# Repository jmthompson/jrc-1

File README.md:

JRC-1
=====

The JRC-1 (Josh's Retro Computer 1) the first in my new series of homebrew
retro computers. It is the first in the JRC series and is the successor to
COLE-1 and COLE-2.

The primary goal for this project is to scale back some of the lofty goals set
for its predecessor, and instead provide some limited expansion capabilities
so that features can be added iteratively down the road.

More information is available on the JRC-1 section of my blog at
https://www.area73.us/jrc-1.

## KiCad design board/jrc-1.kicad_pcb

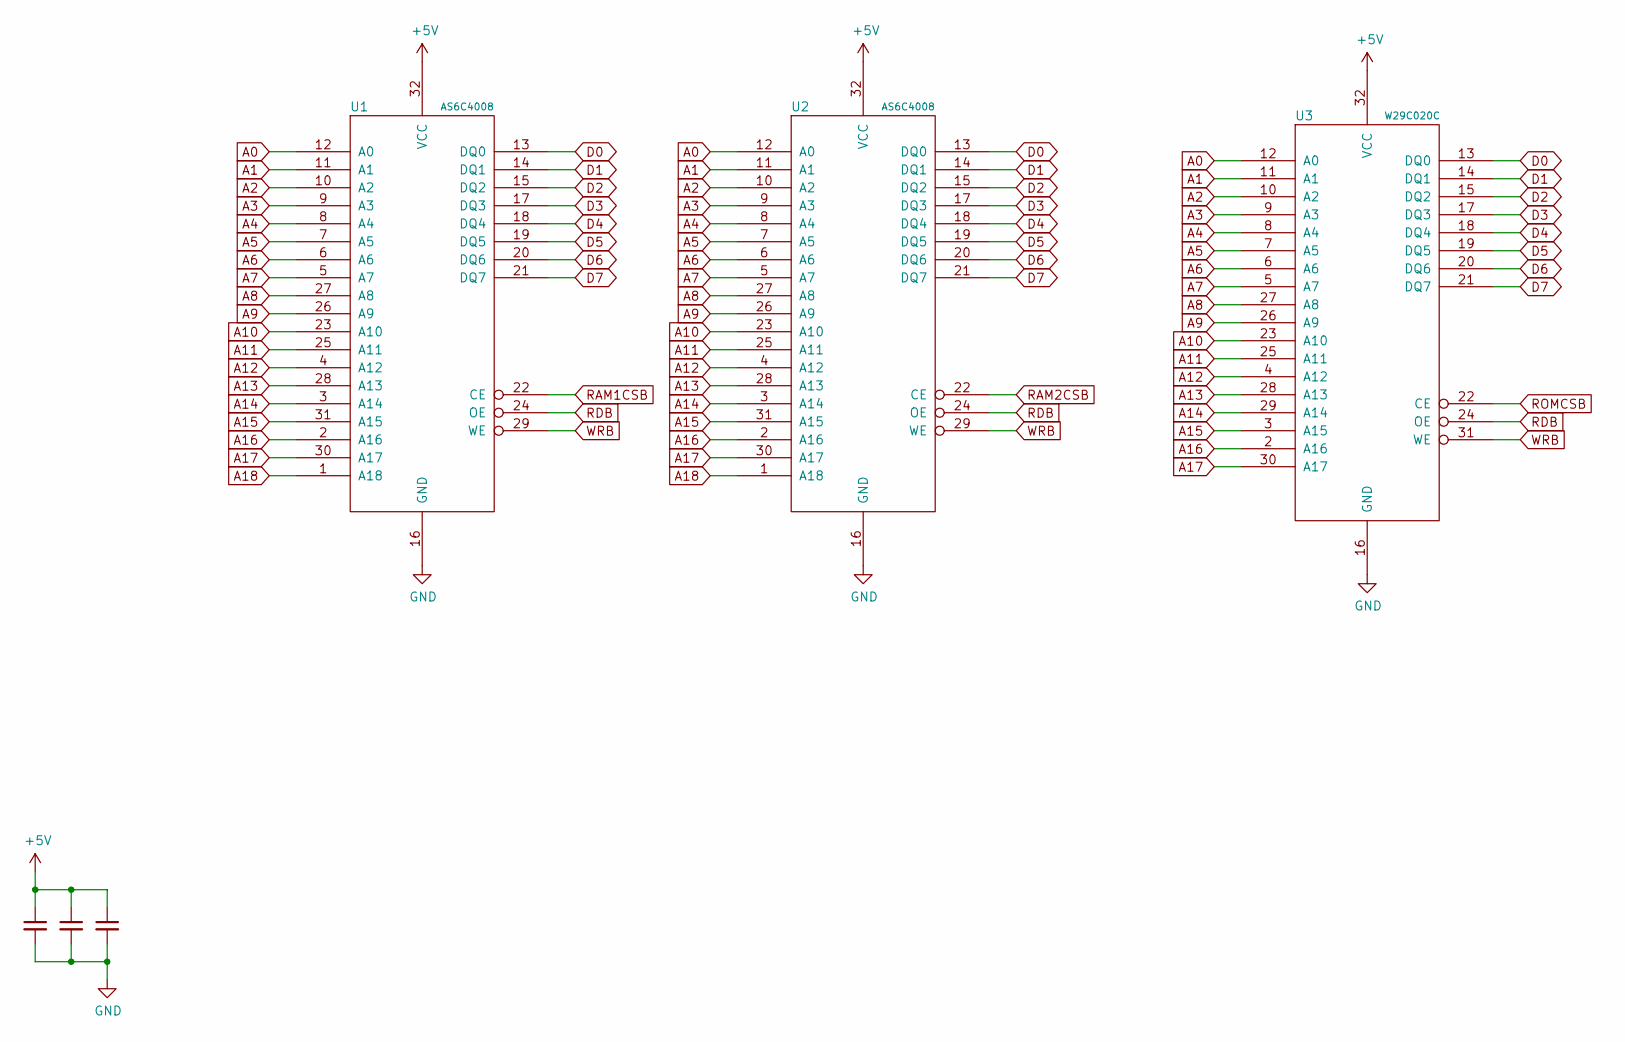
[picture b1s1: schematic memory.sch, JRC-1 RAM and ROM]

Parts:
C1, C2, C3: 0.1u; C_Rect_L4.6mm_W2.0mm_P2.50mm_MKS02_FKP02
U1, U2: AS6C4008; DIP-32_W15.24mm_Socket
U3: W29C020C; DIP_Socket-32_W11.9_W12.7_W15.24_W17.78_W18.5_3M_232-1285-0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

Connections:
+5V: C1.1, C2.1, C3.1, U1.32 (VCC), U2.32 (VCC), U3.32 (VCC); also elsewhere on the board
A0: U1.12 (A0), U2.12 (A0), U3.12 (A0); also elsewhere on the board
A1: U1.11 (A1), U2.11 (A1), U3.11 (A1); also elsewhere on the board
A2: U1.10 (A2), U2.10 (A2), U3.10 (A2); also elsewhere on the board
A3: U1.9 (A3), U2.9 (A3), U3.9 (A3); also elsewhere on the board
A4: U1.8 (A4), U2.8 (A4), U3.8 (A4); also elsewhere on the board
A5: U1.7 (A5), U2.7 (A5), U3.7 (A5); also elsewhere on the board
A6: U1.6 (A6), U2.6 (A6), U3.6 (A6); also elsewhere on the board
A7: U1.5 (A7), U2.5 (A7), U3.5 (A7); also elsewhere on the board
A8: U1.27 (A8), U2.27 (A8), U3.27 (A8); also elsewhere on the board
A9: U1.26 (A9), U2.26 (A9), U3.26 (A9); also elsewhere on the board
A10: U1.23 (A10), U2.23 (A10), U3.23 (A10); also elsewhere on the board
A11: U1.25 (A11), U2.25 (A11), U3.25 (A11); also elsewhere on the board
A12: U1.4 (A12), U2.4 (A12), U3.4 (A12); also elsewhere on the board
A13: U1.28 (A13), U2.28 (A13), U3.28 (A13); also elsewhere on the board
A14: U1.3 (A14), U2.3 (A14), U3.29 (A14); also elsewhere on the board
A15: U1.31 (A15), U2.31 (A15), U3.3 (A15); also elsewhere on the board
A16: U1.2 (A16), U2.2 (A16), U3.2 (A16); also elsewhere on the board
A17: U1.30 (A17), U2.30 (A17), U3.30 (A17); also elsewhere on the board
A18: U1.1 (A18), U2.1 (A18); also elsewhere on the board
D0: U1.13 (DQ0), U2.13 (DQ0), U3.13 (DQ0); also elsewhere on the board
D1: U1.14 (DQ1), U2.14 (DQ1), U3.14 (DQ1); also elsewhere on the board
D2: U1.15 (DQ2), U2.15 (DQ2), U3.15 (DQ2); also elsewhere on the board
D3: U1.17 (DQ3), U2.17 (DQ3), U3.17 (DQ3); also elsewhere on the board
D4: U1.18 (DQ4), U2.18 (DQ4), U3.18 (DQ4); also elsewhere on the board
D5: U1.19 (DQ5), U2.19 (DQ5), U3.19 (DQ5); also elsewhere on the board
D6: U1.20 (DQ6), U2.20 (DQ6), U3.20 (DQ6); also elsewhere on the board
D7: U1.21 (DQ7), U2.21 (DQ7), U3.21 (DQ7); also elsewhere on the board
GND: C1.2, C2.2, C3.2, U1.16 (GND), U2.16 (GND), U3.16 (GND); also elsewhere on the board
RAM1CSB: U1.22 (CE); also elsewhere on the board
RAM2CSB: U2.22 (CE); also elsewhere on the board
RDB: U1.24 (OE), U2.24 (OE), U3.24 (OE); also elsewhere on the board
ROMCSB: U3.22 (CE); also elsewhere on the board
WRB: U1.29 (WE), U2.29 (WE), U3.31 (WE); also elsewhere on the board

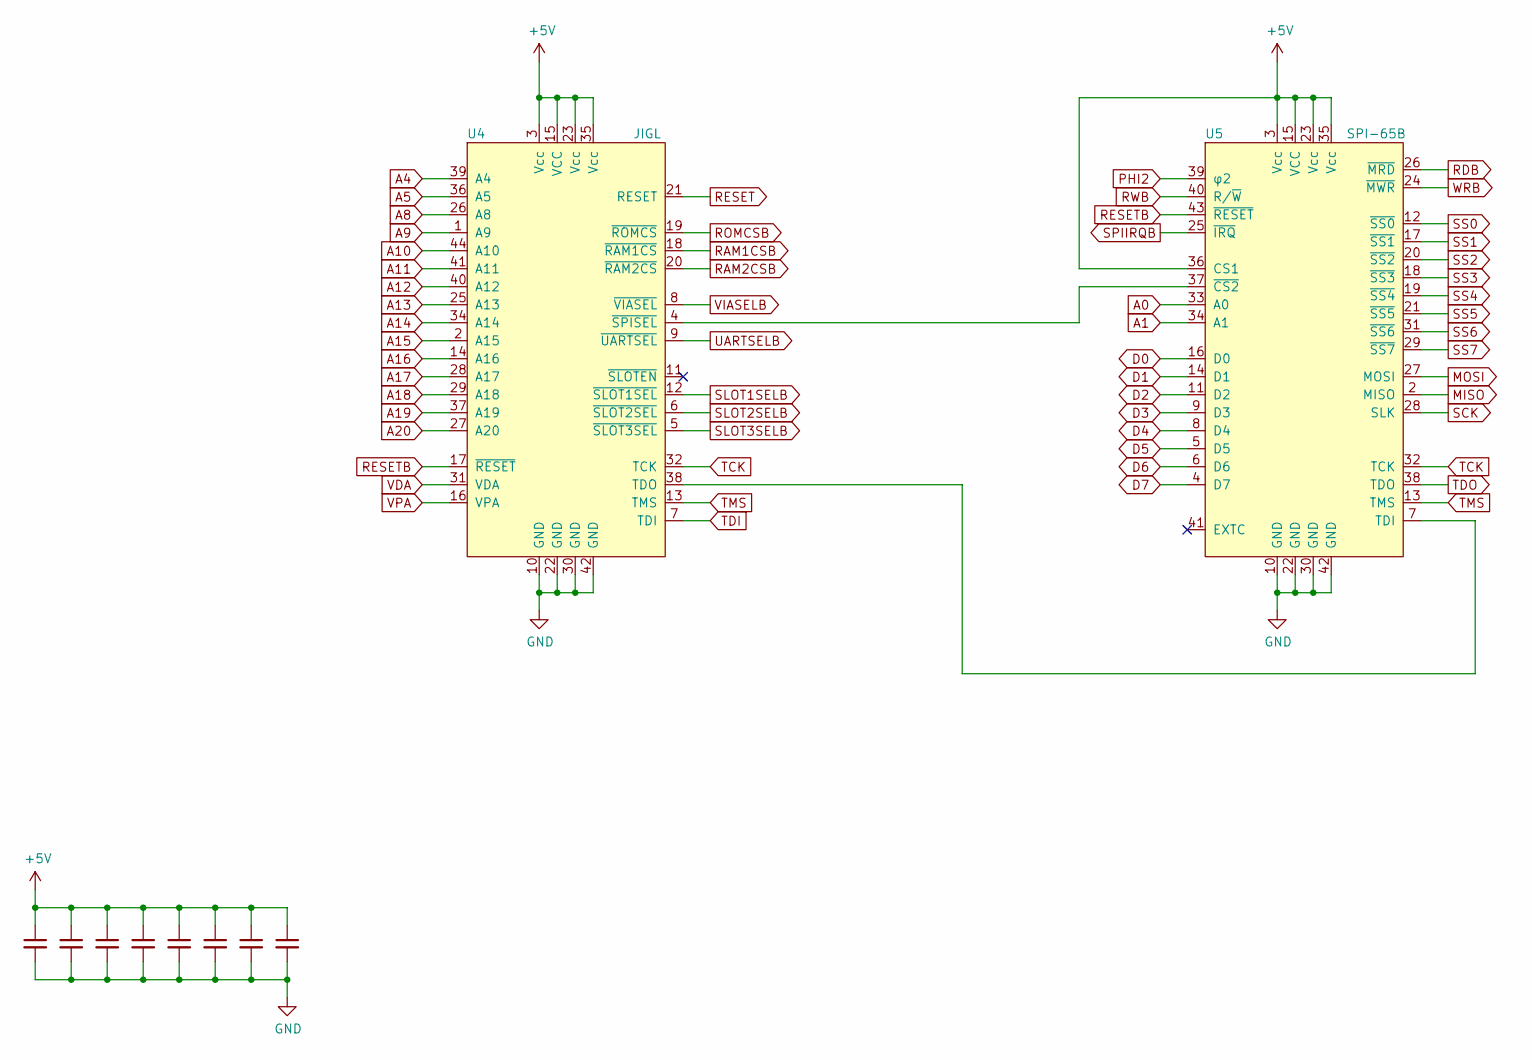
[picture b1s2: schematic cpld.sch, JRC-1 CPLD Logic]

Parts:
C4, C5, C6, C7, C8, C9, C10, C11: 0.1u; C_Rect_L4.6mm_W2.0mm_P2.50mm_MKS02_FKP02
U4: JIGL; PLCC-44_THT-Socket
U5: SPI-65B; PLCC-44_THT-Socket

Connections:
+5V: C4.1, C5.1, C6.1, C7.1, C8.1, C9.1, C10.1, C11.1, U4.3 (Vcc), U4.15 (VCC), U4.23 (Vcc), U4.35 (Vcc), U5.3 (Vcc), U5.15 (VCC), U5.23 (Vcc), U5.35 (Vcc), U5.36 (CS1); also elsewhere on the board
A0: U5.33 (A0); also elsewhere on the board
A1: U5.34 (A1); also elsewhere on the board
A4: U4.39 (A4); also elsewhere on the board
A5: U4.36 (A5); also elsewhere on the board
A8: U4.26 (A8); also elsewhere on the board
A9: U4.1 (A9); also elsewhere on the board
A10: U4.44 (A10); also elsewhere on the board
A11: U4.41 (A11); also elsewhere on the board
A12: U4.40 (A12); also elsewhere on the board
A13: U4.25 (A13); also elsewhere on the board
A14: U4.34 (A14); also elsewhere on the board
A15: U4.2 (A15); also elsewhere on the board
A16: U4.14 (A16); also elsewhere on the board
A17: U4.28 (A17); also elsewhere on the board
A18: U4.29 (A18); also elsewhere on the board
A19: U4.37 (A19); also elsewhere on the board
A20: U4.27 (A20); also elsewhere on the board
D0: U5.16 (D0); also elsewhere on the board
D1: U5.14 (D1); also elsewhere on the board
D2: U5.11 (D2); also elsewhere on the board
D3: U5.9 (D3); also elsewhere on the board
D4: U5.8 (D4); also elsewhere on the board
D5: U5.5 (D5); also elsewhere on the board
D6: U5.6 (D6); also elsewhere on the board
D7: U5.4 (D7); also elsewhere on the board
GND: C4.2, C5.2, C6.2, C7.2, C8.2, C9.2, C10.2, C11.2, U4.10 (GND), U4.22 (GND), U4.30 (GND), U4.42 (GND), U5.10 (GND), U5.22 (GND), U5.30 (GND), U5.42 (GND); also elsewhere on the board
MISO: U5.2 (MISO); also elsewhere on the board
MOSI: U5.27 (MOSI); also elsewhere on the board
unnamed: U4.4 (~SPISEL), U5.37 (~CS2)
unnamed: U4.38 (TDO), U5.7 (TDI)
PHI2: U5.39 (φ2); also elsewhere on the board
RAM1CSB: U4.18 (~RAM1CS); also elsewhere on the board
RAM2CSB: U4.20 (~RAM2CS); also elsewhere on the board
RDB: U5.26 (~MRD); also elsewhere on the board
RESET: U4.21 (RESET); also elsewhere on the board
RESETB: U4.17 (~RESET), U5.43 (~RESET); also elsewhere on the board
ROMCSB: U4.19 (~ROMCS); also elsewhere on the board
RWB: U5.40 (R/~W); also elsewhere on the board
SCK: U5.28 (SLK); also elsewhere on the board
SLOT1SELB: U4.12 (~SLOT1SEL); also elsewhere on the board
SLOT2SELB: U4.6 (~SLOT2SEL); also elsewhere on the board
SLOT3SELB: U4.5 (~SLOT3SEL); also elsewhere on the board
SPIIRQB: U5.25 (~IRQ); also elsewhere on the board
SS0: U5.12 (~SS0); also elsewhere on the board
SS1: U5.17 (~SS1); also elsewhere on the board
SS2: U5.20 (~SS2); also elsewhere on the board
SS3: U5.18 (~SS3); also elsewhere on the board
SS4: U5.19 (~SS4); also elsewhere on the board
SS5: U5.21 (~SS5); also elsewhere on the board
SS6: U5.31 (~SS6); also elsewhere on the board
SS7: U5.29 (~SS7); also elsewhere on the board
TCK: U4.32 (TCK), U5.32 (TCK); also elsewhere on the board
TDI: U4.7 (TDI); also elsewhere on the board
TDO: U5.38 (TDO); also elsewhere on the board
TMS: U4.13 (TMS), U5.13 (TMS); also elsewhere on the board
UARTSELB: U4.9 (~UARTSEL); also elsewhere on the board
VDA: U4.31 (VDA); also elsewhere on the board
VIASELB: U4.8 (~VIASEL); also elsewhere on the board
VPA: U4.16 (VPA); also elsewhere on the board
WRB: U5.24 (~MWR); also elsewhere on the board

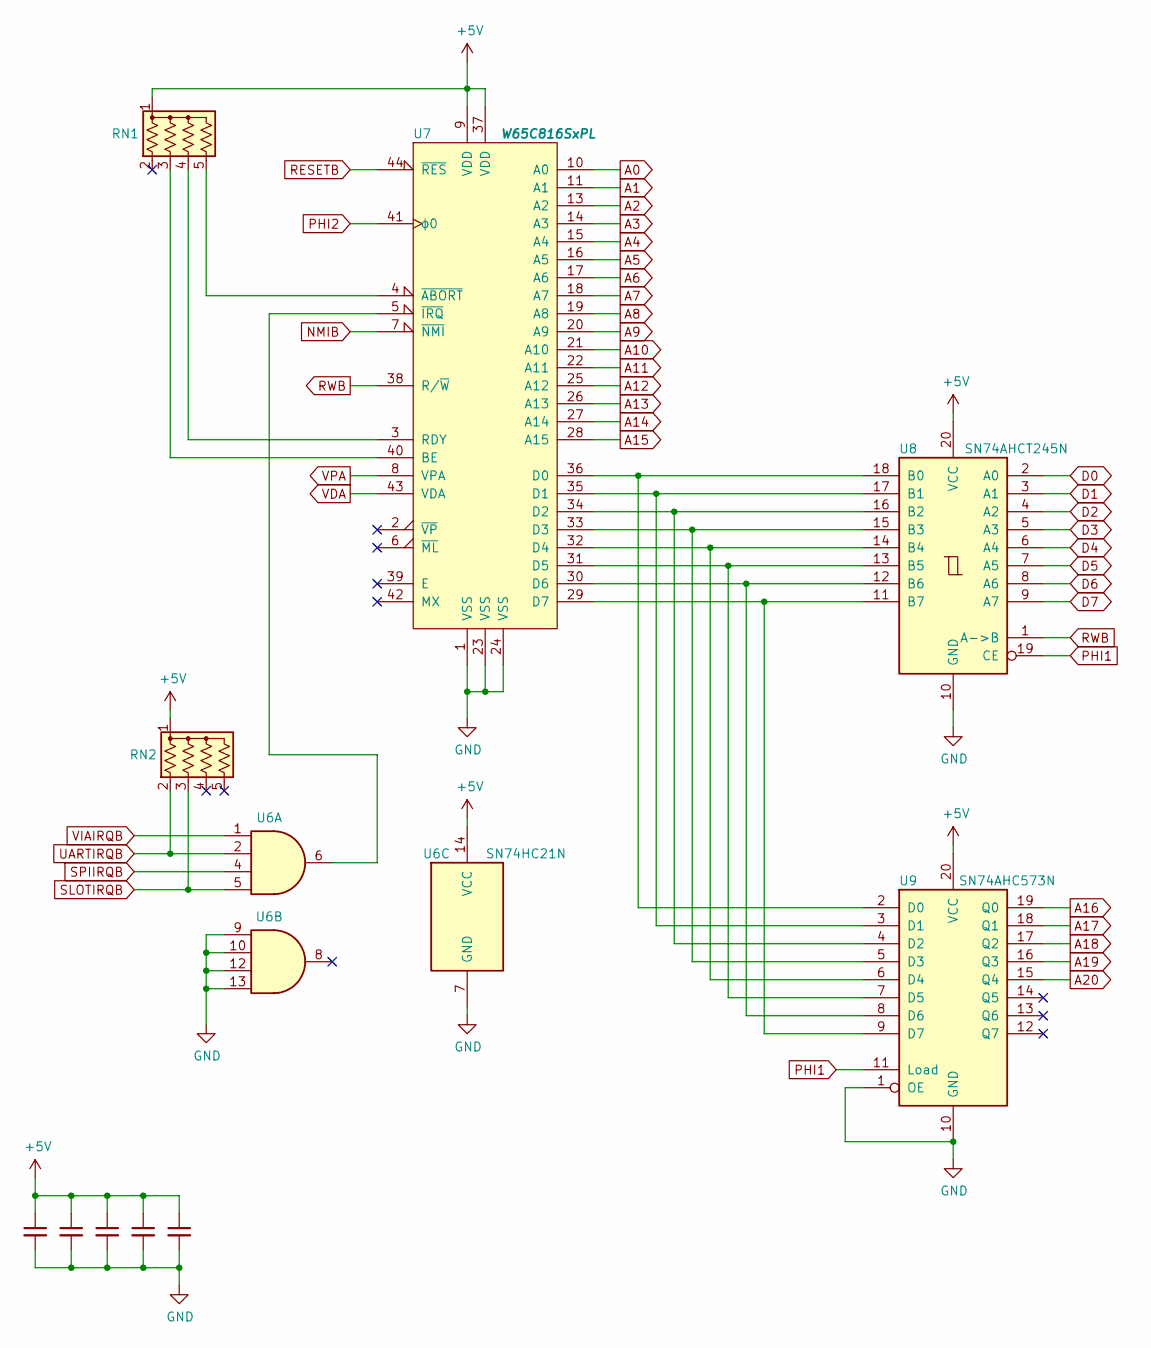
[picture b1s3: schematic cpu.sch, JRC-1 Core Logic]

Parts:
C12, C13, C14, C15, C16: 0.1u; C_Rect_L4.6mm_W2.0mm_P2.50mm_MKS02_FKP02
RN1, RN2: 4605X-101-332LF; R_Array_SIP5
U6: SN74HC21N; DIP-14_W7.62mm_Socket
U7: W65C816SxPL; PLCC-44_THT-Socket
U8: SN74AHCT245N; DIP-20_W7.62mm_Socket
U9: SN74AHC573N; DIP-20_W7.62mm_Socket

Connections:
+5V: C12.1, C13.1, C14.1, C15.1, C16.1, RN1.1 (common), RN2.1 (common), U6.14 (VCC), U7.9 (VDD), U7.37 (VDD), U8.20 (VCC), U9.20 (VCC); also elsewhere on the board
A0: U7.10 (A0); also elsewhere on the board
A1: U7.11 (A1); also elsewhere on the board
A2: U7.13 (A2); also elsewhere on the board
A3: U7.14 (A3); also elsewhere on the board
A4: U7.15 (A4); also elsewhere on the board
A5: U7.16 (A5); also elsewhere on the board
A6: U7.17 (A6); also elsewhere on the board
A7: U7.18 (A7); also elsewhere on the board
A8: U7.19 (A8); also elsewhere on the board
A9: U7.20 (A9); also elsewhere on the board
A10: U7.21 (A10); also elsewhere on the board
A11: U7.22 (A11); also elsewhere on the board
A12: U7.25 (A12); also elsewhere on the board
A13: U7.26 (A13); also elsewhere on the board
A14: U7.27 (A14); also elsewhere on the board
A15: U7.28 (A15); also elsewhere on the board
A16: U9.19 (Q0); also elsewhere on the board
A17: U9.18 (Q1); also elsewhere on the board
A18: U9.17 (Q2); also elsewhere on the board
A19: U9.16 (Q3); also elsewhere on the board
A20: U9.15 (Q4); also elsewhere on the board
D0: U8.2 (A0); also elsewhere on the board
D1: U8.3 (A1); also elsewhere on the board
D2: U8.4 (A2); also elsewhere on the board
D3: U8.5 (A3); also elsewhere on the board
D4: U8.6 (A4); also elsewhere on the board
D5: U8.7 (A5); also elsewhere on the board
D6: U8.8 (A6); also elsewhere on the board
D7: U8.9 (A7); also elsewhere on the board
GND: C12.2, C13.2, C14.2, C15.2, C16.2, U6.7 (GND), U6.9, U6.10, U6.12, U6.13, U7.1 (VSS), U7.23 (VSS), U7.24 (VSS), U8.10 (GND), U9.1 (OE), U9.10 (GND); also elsewhere on the board
NMIB: U7.7 (~NMI); also elsewhere on the board
unnamed: RN1.3 (R2), U7.40 (BE)
unnamed: RN1.4 (R3), U7.3 (RDY)
unnamed: RN1.5 (R4), U7.4 (~ABORT)
unnamed: U6.6, U7.5 (~IRQ)
unnamed: U7.29 (D7), U8.11 (B7), U9.9 (D7)
unnamed: U7.30 (D6), U8.12 (B6), U9.8 (D6)
unnamed: U7.31 (D5), U8.13 (B5), U9.7 (D5)
unnamed: U7.32 (D4), U8.14 (B4), U9.6 (D4)
unnamed: U7.33 (D3), U8.15 (B3), U9.5 (D3)
unnamed: U7.34 (D2), U8.16 (B2), U9.4 (D2)
unnamed: U7.35 (D1), U8.17 (B1), U9.3 (D1)
unnamed: U7.36 (D0), U8.18 (B0), U9.2 (D0)
PHI1: U8.19 (CE), U9.11 (Load); also elsewhere on the board
PHI2: U7.41 (ϕ0); also elsewhere on the board
RESETB: U7.44 (~RES); also elsewhere on the board
RWB: U7.38 (R/~W), U8.1 (A->B); also elsewhere on the board
SLOTIRQB: RN2.3 (R2), U6.5; also elsewhere on the board
SPIIRQB: U6.4; also elsewhere on the board
UARTIRQB: RN2.2 (R1), U6.2; also elsewhere on the board
VDA: U7.43 (VDA); also elsewhere on the board
VIAIRQB: U6.1; also elsewhere on the board
VPA: U7.8 (VPA); also elsewhere on the board

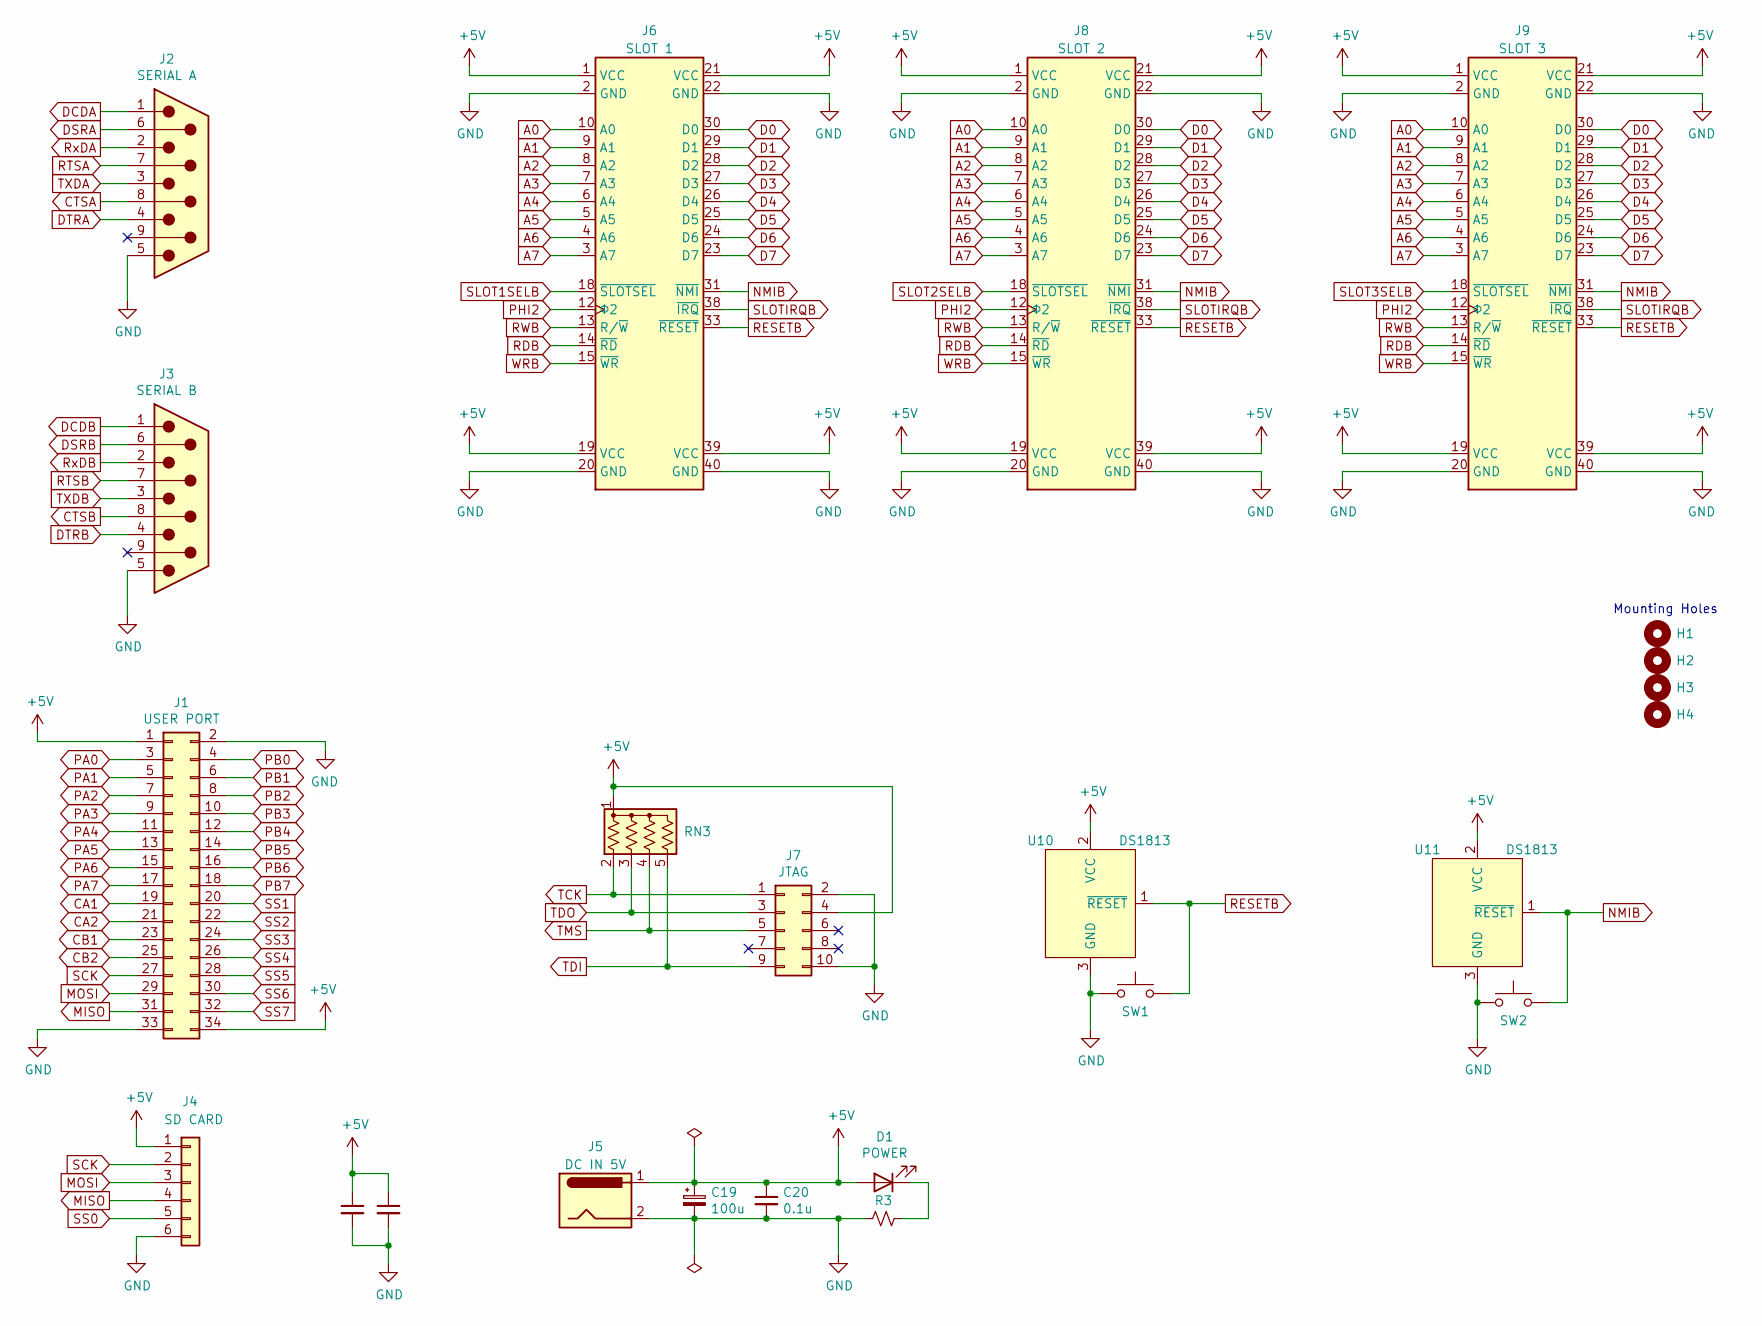
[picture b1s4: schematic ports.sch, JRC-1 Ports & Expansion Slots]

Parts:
C17, C18, C20: 0.1u; C_Rect_L4.6mm_W2.0mm_P2.50mm_MKS02_FKP02
C19: 100u; CP_Radial_D6.3mm_P2.50mm
D1: POWER; LED_D5.0mm_Clear
H1, H2, H3, H4: MountingHole; MountingHole_2.7mm_M2.5
J1: USER PORT; PinHeader_2x17_P2.54mm_Vertical
J2: SERIAL A; DSUB-9_Male_Horizontal_P2.77x2.84mm_EdgePinOffset4.94mm_Hou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
J3: SERIAL B; DSUB-9_Male_Horizontal_P2.77x2.84mm_EdgePinOffset4.94mm_Hou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
J4: SD CARD; PinHeader_1x06_P2.54mm_Vertical
J5: DC IN 5V; BarrelJack_Horizontal
J6: SLOT 1; JRC_Expansion_Slot
J7: JTAG; IDC-Header_2x05_P2.54mm_Vertical
J8: SLOT 2; JRC_Expansion_Slot
J9: SLOT 3; JRC_Expansion_Slot
R3: 330; R_Axial_DIN0207_L6.3mm_D2.5mm_P10.16mm_Horizontal
RN3: 4605X-101-472LF; R_Array_SIP5
SW1: RESET; SW_PUSH_6mm_H5mm
SW2: NMI; SW_PUSH_6mm_H5mm
U10, U11: DS1813; TO-92

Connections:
+5V: C17.1, C18.1, C19.1, C20.1, D1.2 (A), J1.1, J1.34, J4.1, J5.1, J6.1 (VCC), J6.19 (VCC), J6.21 (VCC), J6.39 (VCC), J7.4, J8.1 (VCC), J8.19 (VCC), J8.21 (VCC), J8.39 (VCC), J9.1 (VCC), J9.19 (VCC), J9.21 (VCC), J9.39 (VCC), RN3.1 (common), U10.2 (VCC), U11.2 (VCC); also elsewhere on the board
A0: J6.10 (A0), J8.10 (A0), J9.10 (A0); also elsewhere on the board
A1: J6.9 (A1), J8.9 (A1), J9.9 (A1); also elsewhere on the board
A2: J6.8 (A2), J8.8 (A2), J9.8 (A2); also elsewhere on the board
A3: J6.7 (A3), J8.7 (A3), J9.7 (A3); also elsewhere on the board
A4: J6.6 (A4), J8.6 (A4), J9.6 (A4); also elsewhere on the board
A5: J6.5 (A5), J8.5 (A5), J9.5 (A5); also elsewhere on the board
A6: J6.4 (A6), J8.4 (A6), J9.4 (A6); also elsewhere on the board
A7: J6.3 (A7), J8.3 (A7), J9.3 (A7); also elsewhere on the board
CA1: J1.19; also elsewhere on the board
CA2: J1.21; also elsewhere on the board
CB1: J1.23; also elsewhere on the board
CB2: J1.25; also elsewhere on the board
CTSA: J2.8; also elsewhere on the board
CTSB: J3.8; also elsewhere on the board
D0: J6.30 (D0), J8.30 (D0), J9.30 (D0); also elsewhere on the board
D1: J6.29 (D1), J8.29 (D1), J9.29 (D1); also elsewhere on the board
D2: J6.28 (D2), J8.28 (D2), J9.28 (D2); also elsewhere on the board
D3: J6.27 (D3), J8.27 (D3), J9.27 (D3); also elsewhere on the board
D4: J6.26 (D4), J8.26 (D4), J9.26 (D4); also elsewhere on the board
D5: J6.25 (D5), J8.25 (D5), J9.25 (D5); also elsewhere on the board
D6: J6.24 (D6), J8.24 (D6), J9.24 (D6); also elsewhere on the board
D7: J6.23 (D7), J8.23 (D7), J9.23 (D7); also elsewhere on the board
DCDA: J2.1; also elsewhere on the board
DCDB: J3.1; also elsewhere on the board
DSRA: J2.6; also elsewhere on the board
DSRB: J3.6; also elsewhere on the board
DTRA: J2.4; also elsewhere on the board
DTRB: J3.4; also elsewhere on the board
GND: C17.2, C18.2, C19.2, C20.2, J1.2, J1.33, J2.5, J3.5, J4.6, J5.2, J6.2 (GND), J6.20 (GND), J6.22 (GND), J6.40 (GND), J7.2, J7.10, J8.2 (GND), J8.20 (GND), J8.22 (GND), J8.40 (GND), J9.2 (GND), J9.20 (GND), J9.22 (GND), J9.40 (GND), R3.2, SW1.1, SW2.1, U10.3 (GND), U11.3 (GND); also elsewhere on the board
MISO: J1.31, J4.4; also elsewhere on the board
MOSI: J1.29, J4.3; also elsewhere on the board
NMIB: J6.31 (~NMI), J8.31 (~NMI), J9.31 (~NMI), SW2.2, U11.1 (~RESET); also elsewhere on the board
unnamed: D1.1 (K), R3.1
PA0: J1.3; also elsewhere on the board
PA1: J1.5; also elsewhere on the board
PA2: J1.7; also elsewhere on the board
PA3: J1.9; also elsewhere on the board
PA4: J1.11; also elsewhere on the board
PA5: J1.13; also elsewhere on the board
PA6: J1.15; also elsewhere on the board
PA7: J1.17; also elsewhere on the board
PB0: J1.4; also elsewhere on the board
PB1: J1.6; also elsewhere on the board
PB2: J1.8; also elsewhere on the board
PB3: J1.10; also elsewhere on the board
PB4: J1.12; also elsewhere on the board
PB5: J1.14; also elsewhere on the board
PB6: J1.16; also elsewhere on the board
PB7: J1.18; also elsewhere on the board
PHI2: J6.12 (Φ2), J8.12 (Φ2), J9.12 (Φ2); also elsewhere on the board
RDB: J6.14 (~RD), J8.14 (~RD), J9.14 (~RD); also elsewhere on the board
RESETB: J6.33 (~RESET), J8.33 (~RESET), J9.33 (~RESET), SW1.2, U10.1 (~RESET); also elsewhere on the board
RTSA: J2.7; also elsewhere on the board
RTSB: J3.7; also elsewhere on the board
RWB: J6.13 (R/~W), J8.13 (R/~W), J9.13 (R/~W); also elsewhere on the board
RxDA: J2.2; also elsewhere on the board
RxDB: J3.2; also elsewhere on the board
SCK: J1.27, J4.2; also elsewhere on the board
SLOT1SELB: J6.18 (~SLOTSEL); also elsewhere on the board
SLOT2SELB: J8.18 (~SLOTSEL); also elsewhere on the board
SLOT3SELB: J9.18 (~SLOTSEL); also elsewhere on the board
SLOTIRQB: J6.38 (~IRQ), J8.38 (~IRQ), J9.38 (~IRQ); also elsewhere on the board
SS0: J4.5; also elsewhere on the board
SS1: J1.20; also elsewhere on the board
SS2: J1.22; also elsewhere on the board
SS3: J1.24; also elsewhere on the board
SS4: J1.26; also elsewhere on the board
SS5: J1.28; also elsewhere on the board
SS6: J1.30; also elsewhere on the board
SS7: J1.32; also elsewhere on the board
TCK: J7.1, RN3.2 (R1); also elsewhere on the board
TDI: J7.9, RN3.5 (R4); also elsewhere on the board
TDO: J7.3, RN3.3 (R2); also elsewhere on the board
TMS: J7.5, RN3.4 (R3); also elsewhere on the board
TXDA: J2.3; also elsewhere on the board
TXDB: J3.3; also elsewhere on the board
WRB: J6.15 (~WR), J8.15 (~WR), J9.15 (~WR); also elsewhere on the board

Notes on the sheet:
Mounting Holes

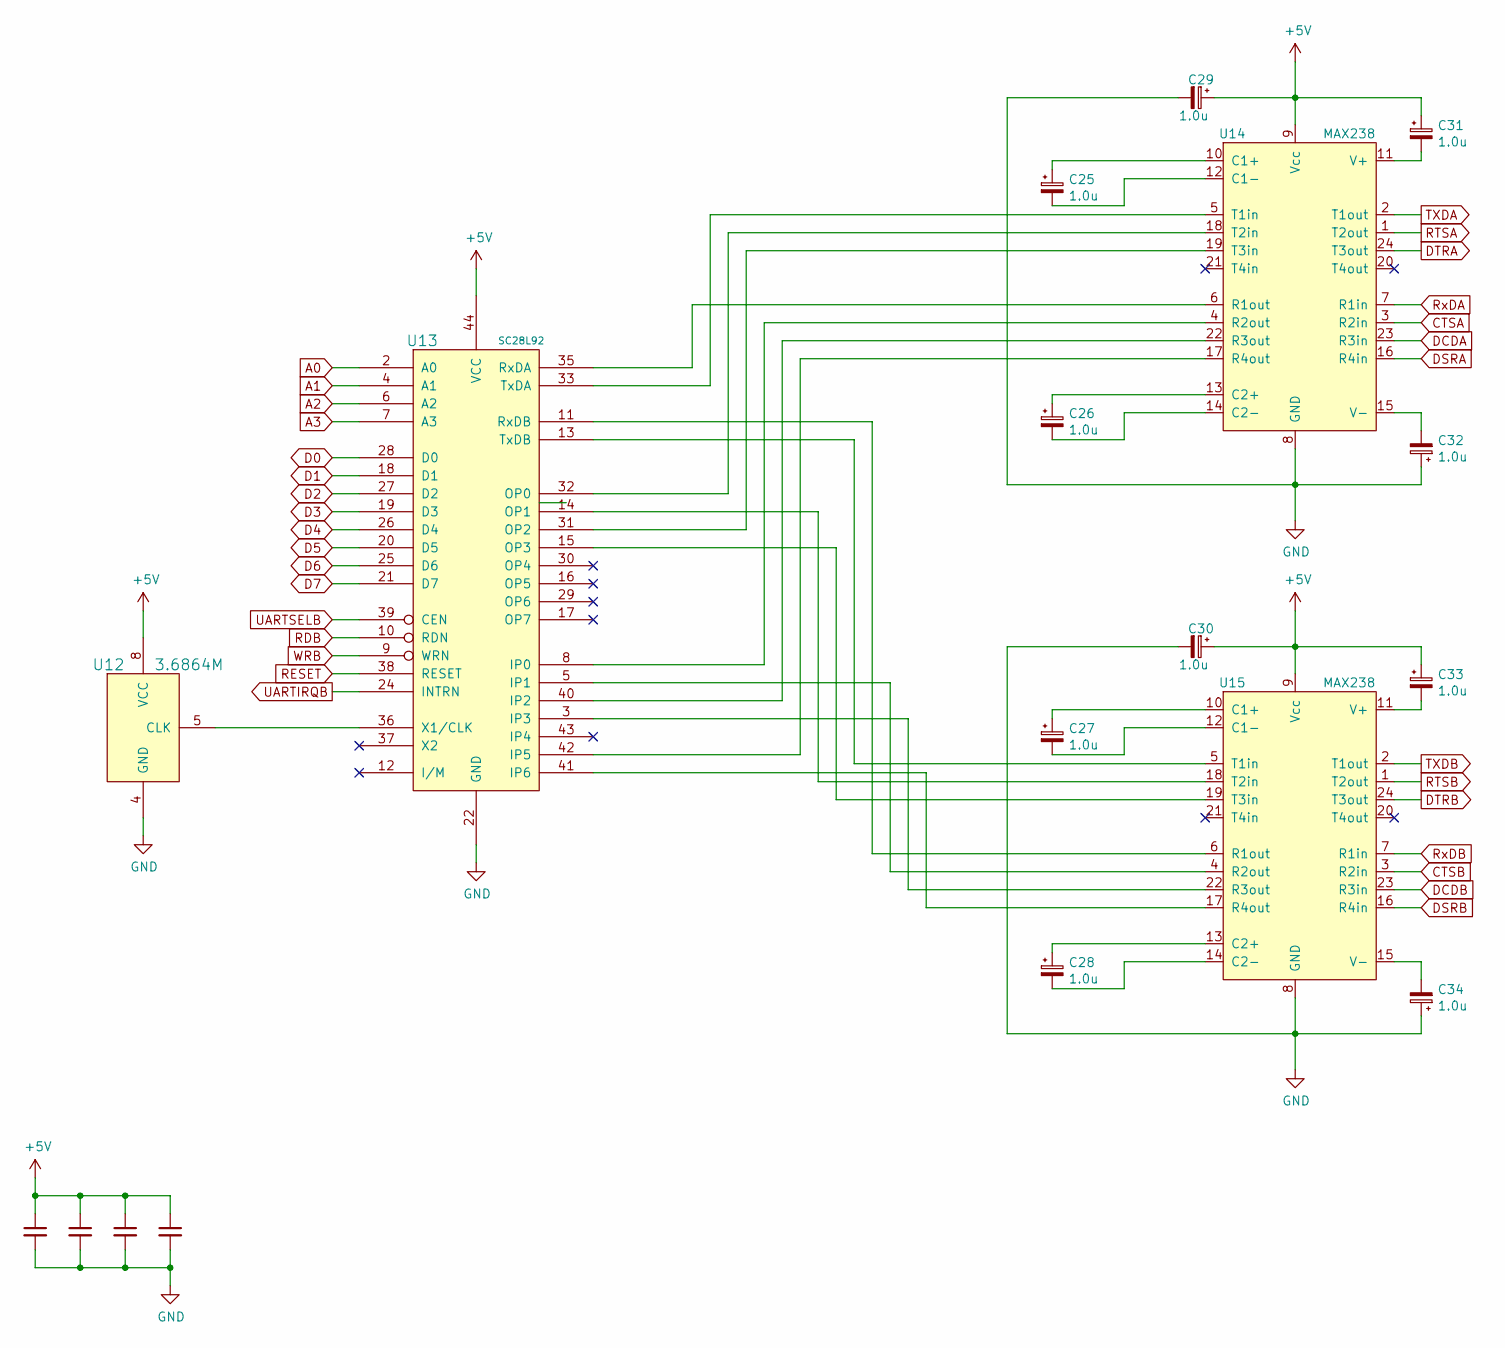
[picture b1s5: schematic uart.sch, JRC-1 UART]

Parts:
C21, C22, C23, C24: 0.1u; C_Rect_L4.6mm_W2.0mm_P2.50mm_MKS02_FKP02
C25, C26, C27, C28, C29, C30, C31, C32, C33, C34: 1.0u; CP_Radial_D5.0mm_P2.00mm
U12: 3.6864M; DIP-8_W7.62mm_Socket
U13: SC28L92; PLCC-44_THT-Socket
U14, U15: MAX238; DIP-24_W7.62mm_Socket

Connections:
+5V: C21.1, C22.1, C23.1, C24.1, C29.1, C30.1, C31.1, C33.1, U12.8 (VCC), U13.44 (VCC), U14.9 (Vcc), U15.9 (Vcc); also elsewhere on the board
A0: U13.2 (A0); also elsewhere on the board
A1: U13.4 (A1); also elsewhere on the board
A2: U13.6 (A2); also elsewhere on the board
A3: U13.7 (A3); also elsewhere on the board
CTSA: U14.3 (R2in); also elsewhere on the board
CTSB: U15.3 (R2in); also elsewhere on the board
D0: U13.28 (D0); also elsewhere on the board
D1: U13.18 (D1); also elsewhere on the board
D2: U13.27 (D2); also elsewhere on the board
D3: U13.19 (D3); also elsewhere on the board
D4: U13.26 (D4); also elsewhere on the board
D5: U13.20 (D5); also elsewhere on the board
D6: U13.25 (D6); also elsewhere on the board
D7: U13.21 (D7); also elsewhere on the board
DCDA: U14.23 (R3in); also elsewhere on the board
DCDB: U15.23 (R3in); also elsewhere on the board
DSRA: U14.16 (R4in); also elsewhere on the board
DSRB: U15.16 (R4in); also elsewhere on the board
DTRA: U14.24 (T3out); also elsewhere on the board
DTRB: U15.24 (T3out); also elsewhere on the board
GND: C21.2, C22.2, C23.2, C24.2, C29.2, C30.2, C32.1, C34.1, U12.4 (GND), U13.22 (GND), U14.8 (GND), U15.8 (GND); also elsewhere on the board
unnamed: C25.1, U14.10 (C1+)
unnamed: C25.2, U14.12 (C1-)
unnamed: C26.1, U14.13 (C2+)
unnamed: C26.2, U14.14 (C2-)
unnamed: C27.1, U15.10 (C1+)
unnamed: C27.2, U15.12 (C1-)
unnamed: C28.1, U15.13 (C2+)
unnamed: C28.2, U15.14 (C2-)
unnamed: C31.2, U14.11 (V+)
unnamed: C32.2, U14.15 (V-)
unnamed: C33.2, U15.11 (V+)
unnamed: C34.2, U15.15 (V-)
unnamed: U12.5 (CLK), U13.36 (X1/CLK)
unnamed: U13.3 (IP3), U15.22 (R3out)
unnamed: U13.5 (IP1), U15.4 (R2out)
unnamed: U13.8 (IP0), U14.4 (R2out)
unnamed: U13.11 (RxDB), U15.6 (R1out)
unnamed: U13.13 (TxDB), U15.5 (T1in)
unnamed: U13.14 (OP1), U15.18 (T2in)
unnamed: U13.15 (OP3), U15.19 (T3in)
unnamed: U13.31 (OP2), U14.19 (T3in)
unnamed: U13.32 (OP0), U14.18 (T2in)
unnamed: U13.33 (TxDA), U14.5 (T1in)
unnamed: U13.35 (RxDA), U14.6 (R1out)
unnamed: U13.40 (IP2), U14.22 (R3out)
unnamed: U13.41 (IP6), U15.17 (R4out)
unnamed: U13.42 (IP5), U14.17 (R4out)
RDB: U13.10 (RDN); also elsewhere on the board
RESET: U13.38 (RESET); also elsewhere on the board
RTSA: U14.1 (T2out); also elsewhere on the board
RTSB: U15.1 (T2out); also elsewhere on the board
RxDA: U14.7 (R1in); also elsewhere on the board
RxDB: U15.7 (R1in); also elsewhere on the board
TXDA: U14.2 (T1out); also elsewhere on the board
TXDB: U15.2 (T1out); also elsewhere on the board
UARTIRQB: U13.24 (INTRN); also elsewhere on the board
UARTSELB: U13.39 (CEN); also elsewhere on the board
WRB: U13.9 (WRN); also elsewhere on the board

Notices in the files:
board/jrc-1.kicad_pcb:
(C) 2021 Joshua M. Thompson
